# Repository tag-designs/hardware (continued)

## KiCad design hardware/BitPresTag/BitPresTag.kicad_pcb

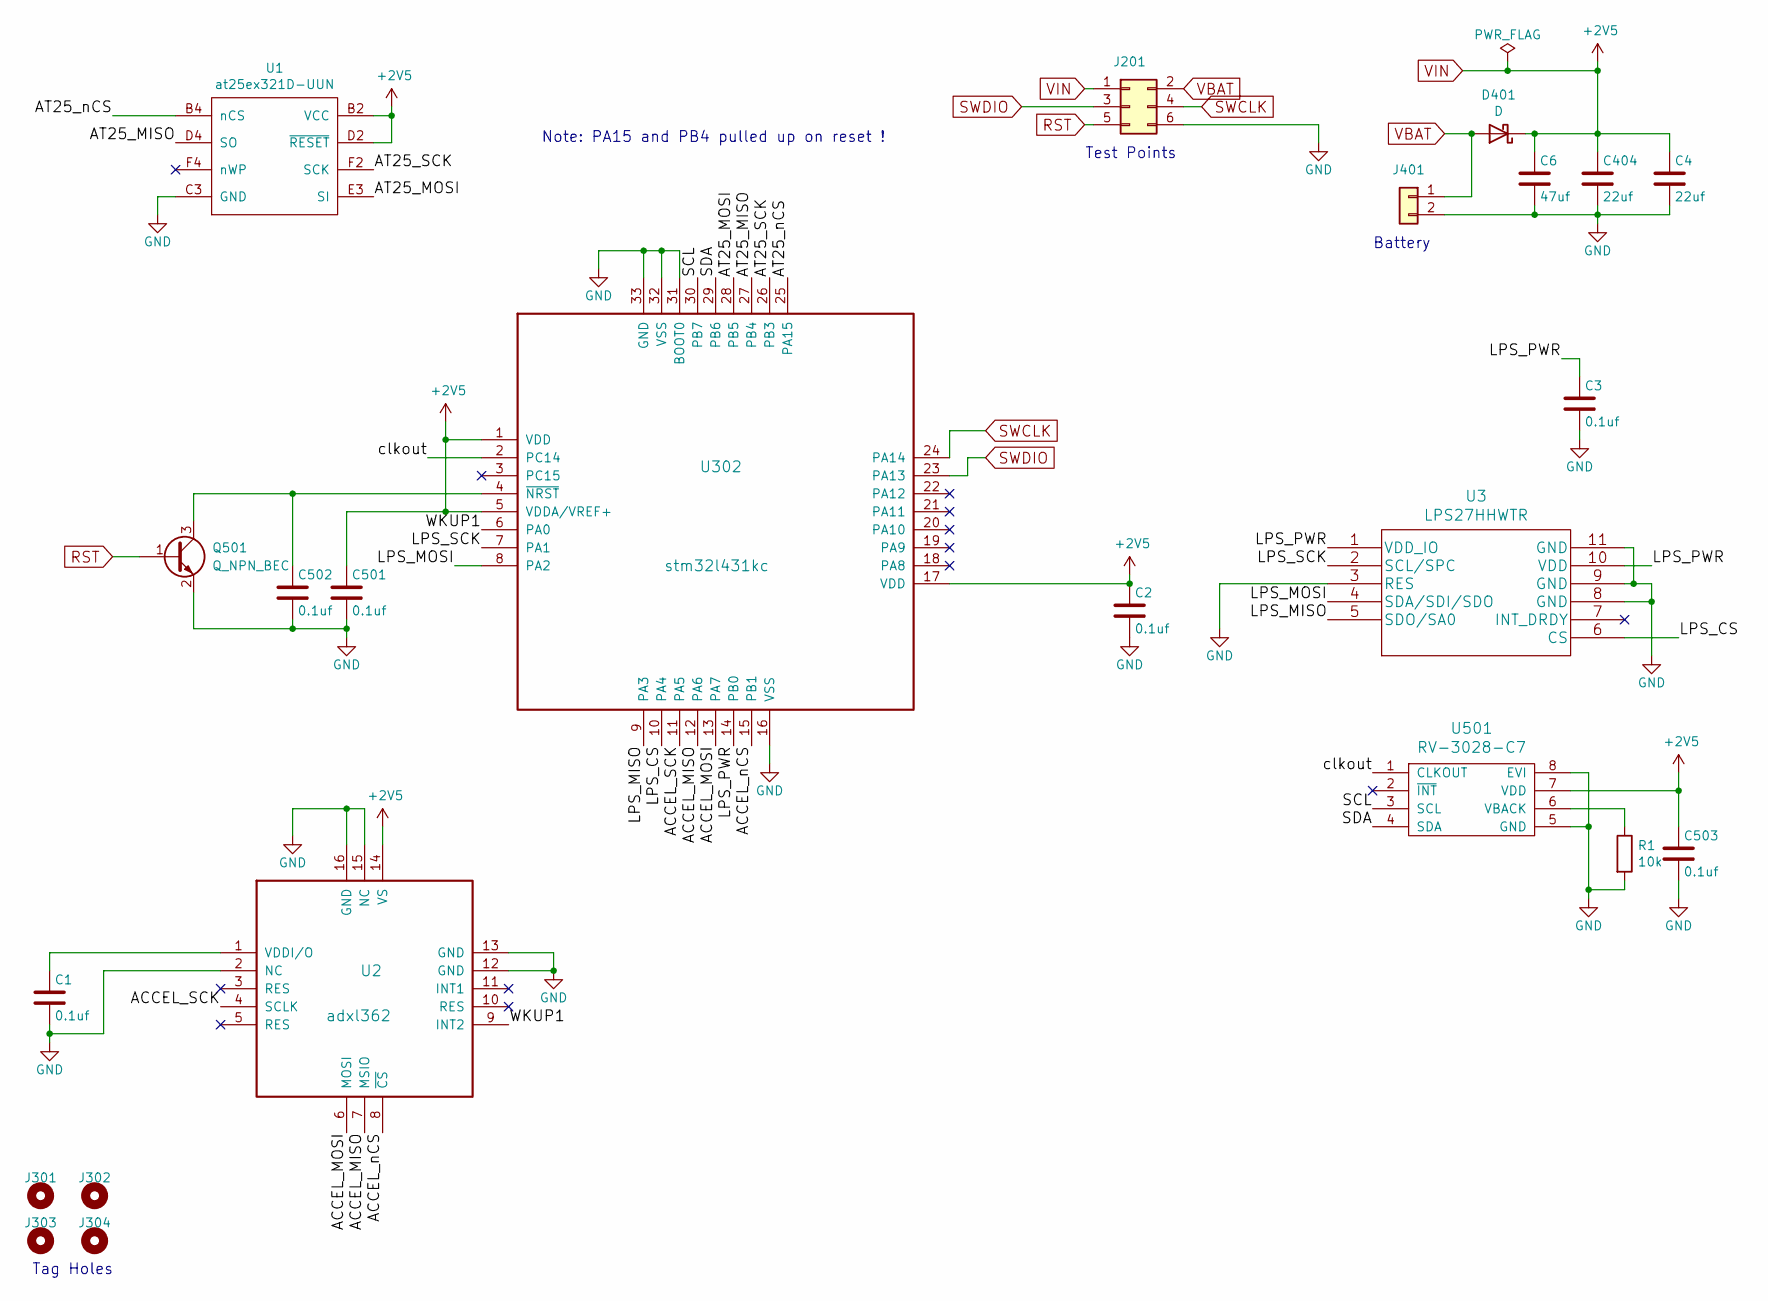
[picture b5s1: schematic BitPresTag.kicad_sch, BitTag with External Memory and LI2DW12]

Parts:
C1: 0.1uf; C_0201_0603Metric; MPN CL05F104ZO5NNNC
C2: 0.1uf; C_0201_0603Metric; MPN GRM033R60J105MEA2D; LCSC C76929
C3: 0.1uf; C_0201_0603Metric; MPN GRM033C81E104KE14D
C4, C404: 22uf; C_0402_1005Metric; MPN 04026D226MAT2A; LCSC C2179118
C6: 47uf; C_0603_1608Metric; MPN 06036D476MAT2A
C501, C502, C503: 0.1uf; C_0201_0603Metric; MPN C181047; LCSC C181047
D401: D; D_0402_1005Metric; MPN CDBQC0130L-HF; LCSC C2886012
J201: CONN_02X04; tagpoints6
J301, J302, J303, J304: Conn_01x01; taghole1.1mm
J401: CONN_01X02; MS621
Q501: Q_NPN_BEC; SOT-883; MPN BC847AMB,315; LCSC C686658
R1: 10k; R_0201_0603Metric; MPN RC0201FR-0710KL; LCSC C106225
U1: at25ex321D-UUN; adesto_wlcsp12; MPN AT25FF321A-UUN-T; LCSC C1858339
U2: adxl362; ADXL362; MPN ADXL362BCCZ-RL7
U3: LPS27HHWTR; MPN LPS27HHTWTR
U302: stm32l431kc; QFN-32-1EP_5x5mm_P0.5mm_EP3.45x3.45mm; MPN STM32L432KCU6; LCSC C1337280
U501: RV-3028-C7; RV-8803-C7; MPN RV-3028-C7 32.768KHZ 1PPM-TA-QA; LCSC C3019759

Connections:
/ACCEL_MISO: U2.7 (MSIO), U302.12 (PA6)
/ACCEL_MOSI: U2.6 (MOSI), U302.13 (PA7)
/ACCEL_SCK: U2.4 (SCLK), U302.11 (PA5)
/ACCEL_nCS: U2.8 (~CS), U302.15 (PB1)
/AT25_MISO: U1.D4 (SO), U302.27 (PB4)
/AT25_MOSI: U1.E3 (SI), U302.28 (PB5)
/AT25_SCK: U1.F2 (SCK), U302.26 (PB3)
/AT25_nCS: U1.B4 (nCS), U302.25 (PA15)
/LPS_CS: U3.6 (CS), U302.10 (PA4)
/LPS_MISO: U3.5 (SDO/SA0), U302.9 (PA3)
/LPS_MOSI: U3.4 (SDA/SDI/SDO), U302.8 (PA2)
/LPS_PWR: C3.1, U3.1 (VDD_IO), U3.10 (VDD), U302.14 (PB0)
/LPS_SCK: U3.2 (SCL/SPC), U302.7 (PA1)
/SCL: U302.30 (PB7), U501.3 (SCL)
/SDA: U302.29 (PB6), U501.4 (SDA)
/WKUP1: U2.9 (INT2), U302.6 (PA0)
/clkout: U302.2 (PC14), U501.1 (CLKOUT)
GND: C1.2, C2.2, C3.2, C4.2, C6.2, C404.2, C501.2, C502.2, C503.2, J201.6, J401.2, Q501.2 (E), R1.2, U1.C3 (GND), U2.2 (NC), U2.12 (GND), U2.13 (GND), U2.15 (NC), U2.16 (GND), U3.3 (RES), U3.8 (GND), U3.9 (GND), U3.11 (GND), U302.16 (VSS), U302.31 (BOOT0), U302.32 (VSS), U302.33 (GND), U501.5 (GND), U501.8 (EVI)
unnamed: C502.1, Q501.3 (C), U302.4 (~NRST)
unnamed: C1.1, U2.1 (VDDI/O)
unnamed: R1.1, U501.6 (VBACK)
RST: J201.5, Q501.1 (B)
SWCLK: J201.4, U302.24 (PA14)
SWDIO: J201.3, U302.23 (PA13)
VBAT: D401.2 (A), J201.2, J401.1
VIN: C2.1, C4.1, C6.1, C404.1, C501.1, C503.1, D401.1 (K), J201.1, U1.B2 (VCC), U1.D2 (~RESET), U2.14 (VS), U302.1 (VDD), U302.5 (VDDA/VREF+), U302.17 (VDD), U501.7 (VDD)

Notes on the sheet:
Note: PA15 and PB4 pulled up on reset !
Tag Holes
Test Points
Battery

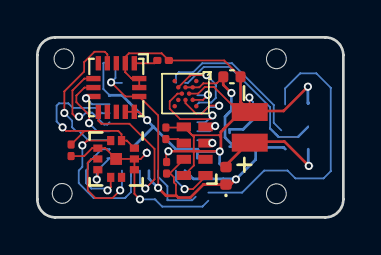
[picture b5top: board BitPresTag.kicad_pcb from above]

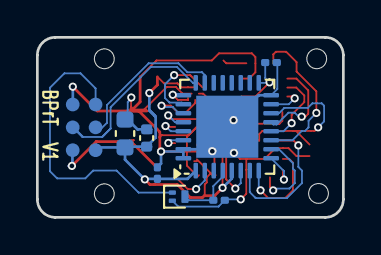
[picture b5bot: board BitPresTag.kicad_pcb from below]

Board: 2 copper layers, 17.0 x 10.0 mm, 23 parts (8 on the bottom side), 26 nets.
